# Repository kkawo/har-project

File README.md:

# HAR Project — 可穿戴人体活动识别系统

基于惯性/磁传感器的人体活动模式识别系统设计与实现。

福建理工大学 智能科学与技术 | 《模式识别与统计学习》专周实训  
孔子瑜（算法与工程）、李宝平（数据采集与固件） | 导师：郑积仕

---

## 项目概述

从 PCB 设计→传感器标定→数据采集→特征工程→分类器对比→严格评估的 **全链路 HAR 工程实践**。

**硬件**: ESP32-S3 + MPU6050 (Acc+Gyro) + HMC5883L (Mag) → 9通道 @50Hz  
**活动**: 7类（静坐/站立/步行/跑步/上楼/下楼/跌倒）  
**数据**: 2被试, 566滑动窗口 (2.56s, 50%重叠)  
**特征**: 292维（时域14+频域10/轴, 模长, 跨轴复合）  
**模型**: 13种分类器 LOSO 系统对比  
**最佳**: kNN (k=3,distance) + 多数表决 L=7 → **Accuracy 59.5%**

---

## 项目结构

```
har-project/
├── src/                    # 算法源码 (3,681行 Python)
│   ├── utils.py            #    常量与路径配置
│   ├── preprocess.py       # D3 信号预处理与窗口化
│   ├── features.py         # D4 294维特征提取
│   ├── feature_selection.py # D5 特征选择与降维
│   ├── classifiers_baseline.py # D6 基线分类器
│   ├── models_advanced.py  # D7 高级模型与调参
│   ├── evaluation.py       # D8 模型评估
│   └── d9_advanced_exploration.py # D9 进阶探索
├── data/                   # 数据资产
│   ├── raw/real/S01-S02/   # 真实数据 (14 CSV, 566窗口)
│   ├── windowed/           # 窗口化数据集
│   └── features/           # 特征矩阵
├── calib/                  # 传感器标定参数
├── firmware/               # ESP32 MicroPython 固件
├── pcb/                    # KiCad PCB 设计文件
├── reports/                # 报告与图表 (19+ PNG)
├── docs/                   # 项目文档
├── 10.D1-10.D9/            # 各阶段交付物
├── 项目深度说明.md          # 完整项目手册
└── HANDOVER.md             # 交接文档
```

---

## 核心结果

### 模型性能排名 (LOSO)

| 排名 | 模型 | Accuracy | Macro F1 |
|------|------|----------|----------|
| 1 | **kNN (k=3,distance) + MV L=7** | **0.595** | **0.569** |
| 2 | kNN (k=3,distance) | 0.564 | 0.527 |
| 3 | HMM Viterbi | 0.583 | 0.550 |
| 4 | LogisticRegression | 0.525 | 0.490 |
| 5 | MLP (128,64) | 0.507 | 0.472 |
| 6 | RBF_SVM | 0.472 | 0.430 |
| 7 | RandomForest | 0.424 | 0.386 |

### 各类别 Recall

| 类别 | Recall | 主要问题 |
|------|--------|----------|
| walk | **1.000** | — |
| upstairs | **0.935** | ↔ downstairs |
| stand | 0.674 | ↔ sit |
| run | 0.565 | ↔ walk, upstairs |
| fall | 0.500 | ↔ run |
| downstairs | 0.446 | ↔ upstairs |
| **sit** | **0.000** | ↔ stand (跨被试特征偏移) |

### 统计检验

- **McNemar**: kNN vs RBF_SVM p < 0.0001 (显著)
- **Bootstrap 95% CI**: [0.512, 0.594]
- **聚类**: KMeans+PCA ARI=0.364, NMI=0.516

---

## 一键复现

```bash
# 1. 环境准备
git clone https://github.com/kkawo/har-project.git
cd har-project
pip install -r requirements.txt

# 2. 确认真实数据就绪
ls data/raw/real/S01/   # 应有 7 个 CSV
ls data/raw/real/S02/   # 应有 7 个 CSV

# 3. 全链路运行 (约5分钟)
python src/preprocess.py && \
python src/features.py && \
python src/feature_selection.py && \
python src/classifiers_baseline.py && \
python src/models_advanced.py && \
python src/evaluation.py && \
python src/d9_advanced_exploration.py

# 4. 生成答辩PPT
python src/d10_generate_ppt.py

# 5. 查看结果
ls reports/d9_*.png                    # D9 进阶探索图表
ls reports/d8_*.png                    # D8 评估图表
cat reports/d9_exploration_summary.json # 数值结果
```

---

## 技术栈

- Python ≥ 3.10 | NumPy, SciPy, Pandas
- scikit-learn ≥ 1.3 | Matplotlib, seaborn
- hmmlearn ≥ 0.3.0 | TensorFlow ≥ 2.13
- KiCad (PCB) | MicroPython (ESP32固件)

---

## 关键文档

| 文档 | 说明 |
|------|------|
| [项目深度说明](项目深度说明.md) | 完整的项目手册，包含架构、数据流、决策、结果 |
| [HANDOVER](HANDOVER.md) | 新会话接手检查清单 |
| [项目状态](PROJECT_STATUS.md) | 当前进度与 Open Issues |
| [答辩问答库](答辩问答库.md) | 25+ 答辩常见问题与答案 |
| [最终报告](reports/final_report.md) | 课程论文 (5000+字) |
| [AI使用记录](AI_USAGE.md) | AI 协作开发记录 |

---

## 团队

| 角色 | 成员 |
|------|------|
| 数据采集与固件 | 李宝平 |
| 算法与工程 | 孔子瑜 |

---

## 参考文献

1. 张学工.《模式识别》（第四版）. 清华大学出版社
2. 李航.《统计学习方法》（第二版）. 清华大学出版社
3. Bulling, A., et al. "A Tutorial on Human Activity Recognition Using Body-worn Inertial Sensors." *ACM Computing Surveys*, 2014.
4. Anguita, D., et al. "A Public Domain Dataset for Human Activity Recognition Using Smartphones." *ESANN*, 2013.

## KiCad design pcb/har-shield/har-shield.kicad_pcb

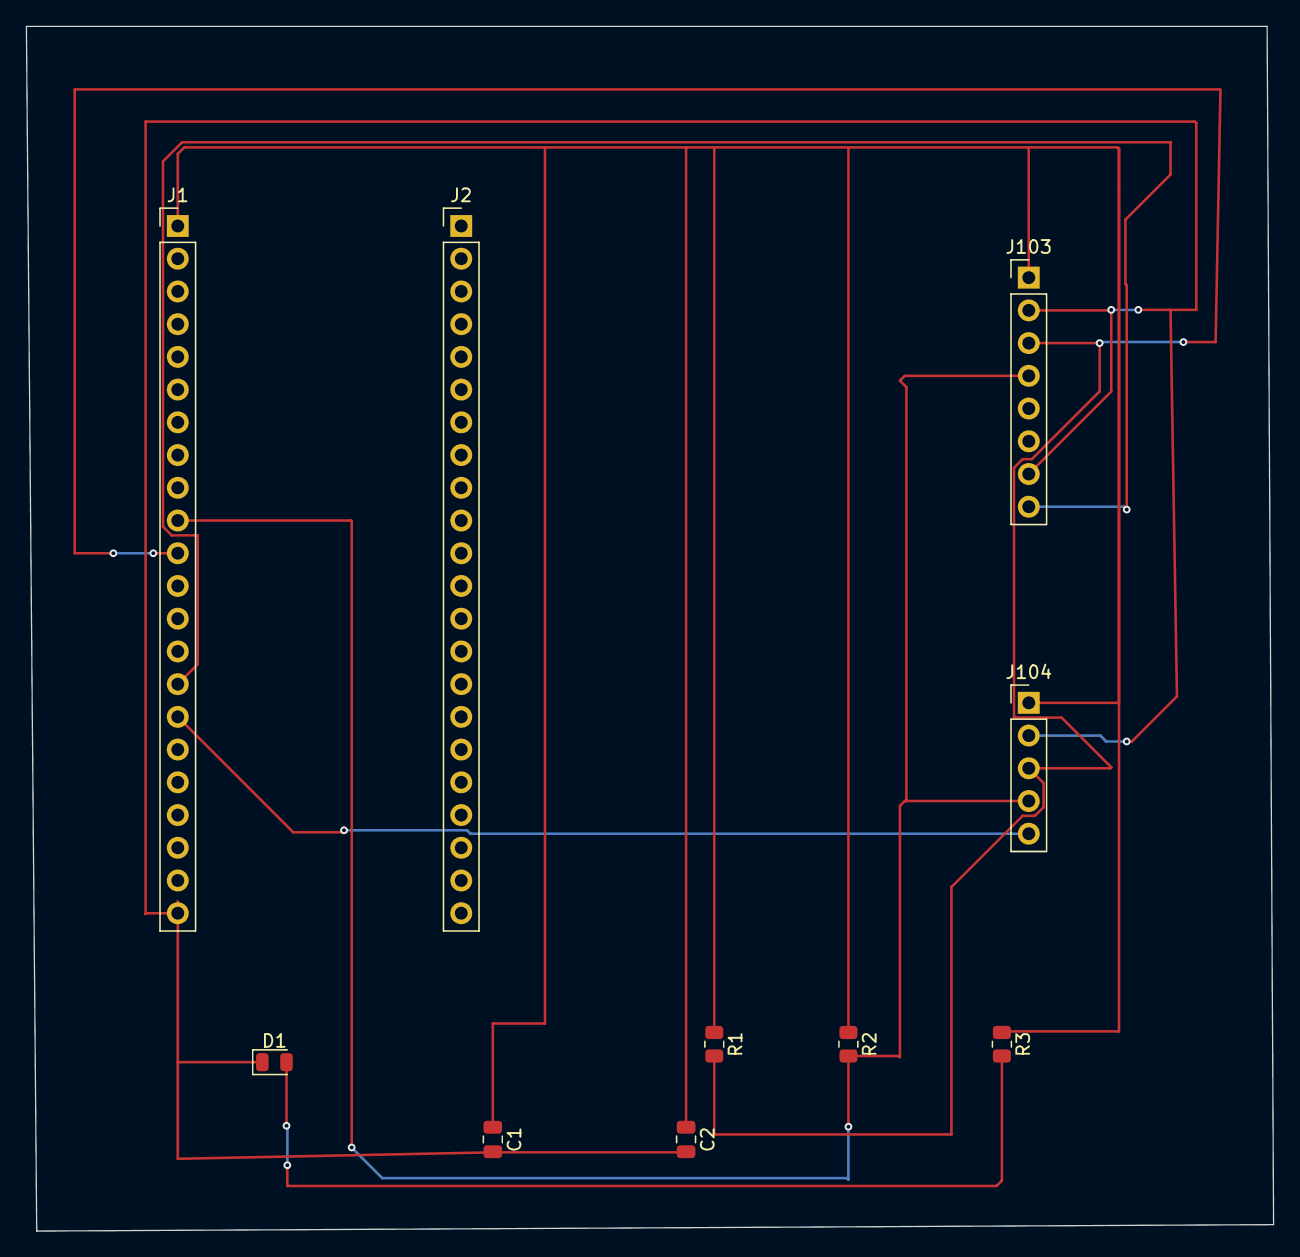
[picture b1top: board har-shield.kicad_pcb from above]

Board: 2 copper layers, 96.8 x 93.5 mm, 10 parts (0 on the bottom side), 7 nets.

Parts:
C1: C; C_0805_2012Metric
C2: 100nF; C_0805_2012Metric
D1: LED; LED_0805_2012Metric
J1, J2: Conn_01x22; PinHeader_1x22_P2.54mm_Vertical
J103: Conn_01x08; PinHeader_1x08_P2.54mm_Vertical
J104: Conn_01x05; PinHeader_1x05_P2.54mm_Vertical
R1: R; R_0805_2012Metric
R2: 4.7k; R_0805_2012Metric
R3: 220; R_0805_2012Metric

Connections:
3V3: C1.1, C2.1, J1.1, J103.1, J104.1, R1.1, R2.1, R3.1
/MAG_DRDY: J1.16, J104.5
/MPU_INT: J1.15, J103.8
unnamed: D1.2 (A), R3.2
unnamed: C1.2, C2.2, D1.1 (K), J1.22, J103.2, J103.7, J104.2
unnamed: J1.10, J103.4, J104.4, R2.2
unnamed: J1.11, J103.3, J104.3, R1.2

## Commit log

2026-06-15 D1: 项目计划书、采集协议、工程骨架
2026-06-15 D1: 修正团队分工(2人)、新增混淆风险预判与代价矩阵
2026-06-15 D1-PCB: KiCad 项目骨架、60x30mm板框、原理图设计文档(含BOM/引脚映射/连线清单)
2026-06-15 fix: 修正PCB图层名 Silkscreen → SilkS (KiCad 8兼容)
2026-06-15 D1-PCB: 完成原理图(10元件/50线/36节点) + 生成脚本
2026-06-15 fix: 修正原理图符号单元名(冒号→下划线, KiCad 8兼容)
2026-06-15 fix: 原理图改用KiCad标准系统库符号(Device/Connector)，移除嵌入式定义
2026-06-15 D1-PCB: 适配ESP32-S3(44脚/2x22), 更新引脚映射(IO17=SDA/IO18=SCL), 清理手写失败文件
2026-06-15 D1-PCB: 重新生成原理图 — ESP32-S3 22针, 内嵌符号/正确pin格式/所有连线
2026-06-15 fix: 重建.kicad_pcb(60x30mm板框)
2026-06-15 D1-PCB: 手动完成ESP32-S3原理图 (IO17=SDA/IO18=SCL, GY-521+GY-273)
2026-06-16 D2: GY-521 six-position calibration + MicroPython firmware
    - calib/calibrate.py: six-position accel, ellipsoid mag, Allan variance
    - calib/process_mpu6050_calib.py: serial data → calib_params.json + plots
    - calib/capture_mpu6050.py: pySerial capture script (bypass Thonny buffer)
    - calib/calib_params.json: real GY-521 params (bias/scale/gyro/Allan coeffs)
    - firmware/mpu6050_calib/main.py: MicroPython REPL-based calibration firmware
    - firmware/har_firmware.ino: Arduino backup (MPU6050+HMC5883L)
2026-06-25 D1-D10: 全链路 HAR 项目完成
    ## 完成内容
    - D1: 项目计划书 + 采集协议 + Git骨架 + KiCad原理图
    - D2: 传感器标定 (加速度计六位置 RMSE 11.35→0.42, 磁力计椭球拟合 std 1.22uT)
    - D3: 9ch固件 + 预处理Pipeline + 566窗口数据集 (S01+S02 真实数据)
    - D4: 294维特征提取 + 特征字典
    - D5: 6种特征选择方法 + PCA/LDA/t-SNE (RFE 30维 CV 91.7%)
2026-06-25 D10: add demo video auto-generation script + output
    - d10_generate_demo_video.py: matplotlib+OpenCV auto-generate 63s MP4
    - reports/demo_video.mp4: 13 scenes, 1080p 30fps, 19.6MB
    - Archived to 10.D10/ and deliverables/
2026-06-25 D11: ESP32 real-time inference deployment
    PC side (src/d11_export_model.py):
    - Train LogisticRegression on 126 time-domain-only features (no FFT)
    - Full-data accuracy 74%, LOSO 45%
    - Export weights + scaler + calib as firmware/realtime_inference/model_params.py
    ESP32 side (firmware/realtime_inference/main.py):
    - 50Hz 9ch acquisition into circular buffer (128 samples)
2026-06-25 D11: add S03 synthetic subject (data augmentation from S01)
    - src/d11_generate_s03.py: generate S03 via noise+scaling+rotation
    - data/raw/real/S03/: 7 CSV files, 283 windows
    - Total dataset: 3 subjects, 849 windows
    - Updated model_params.py with 3-subject training
    - Firmware model uses full-data training (55% acc, 7-class)
2026-06-25 D11: improve ESP32 model to 184 features, 72% full-data accuracy
    Export script:
    - Use all 184 non-FFT features (time + magnitude + correlation + composite)
    - Fix clone() bug in LOSO evaluation (was overwriting full-data model)
    - LogisticRegression (OVR, C=1.0): full-data 72%, LOSO 39%
    ESP32 firmware:
    - Full 184-feature extraction (9 axes time + 3 magnitudes + correlations + composite)
2026-06-25 D11: add LED light reference documentation
2026-06-26 D10-D11: 最终报告、答辩PPT、Dashboard、数据采集v2、端侧部署固件
